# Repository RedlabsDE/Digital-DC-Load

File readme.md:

# Digtial DC Load Project

**key features:**
- linear constant curren sink
- galvanic isolated
- selectable operating range (high/low current/voltage)
- controlled via I2C
	- write & read load current
	- read load voltage
	- read additional external voltage
	- read temperature 
- manual option: set current via external voltage (or potentiometer)

**example application:**
- charge / discharge battery (control & measure current and voltage)
- measure & log current/voltage (use example setup to send data to PC)
- stess test of power supply

## Repository Overview
- **documentation**
  - application notes for constant current sink 
  - block diagram of PCB
  - screenshots and pictures of this project
- **firmware**
  - Arduino Example Project `DigitalLoadExample`, inlcuding a C++ class `RL021_DigitalLoad` for easy control
  - Example calibration procedure (manually step by step)
- **hardware**
  - **KiCAD** Project Folder including schematic, PCB layout and BOM
  - **schematic** and fabrication layer drawing as PDF
  - **datasheet** of used components
- **ui**
  - **GUI_CSS** is an example project for a simple pc-based user interface (written in processing)

## Hardware

**Order PCB:** https://aisler.net/p/YHESFYKF

### Jumper Settings
Via multiple jumpers the used operating ranges can be configured.

| Parameter | Jumper | open | closed |
| -- | -- | -- | -- |
| Current Control | JP1 | External analog signal | Digital via onboard DAC |
| I_load range | JP2 | low 0-1A | high 0-10A |
| V_load range | JP3 | high 0-24V | 0-4V |
| V_extern range | JP4 | high 0-24V | 0-4V |
| ADC I2C Addr (A2,A1,A0)| R8 | 0,0,1 | 0,0,0 |

# Example Setup

## Example Arduino Control

### Connect Arduino to CCS-PCB
| Signal      	| Arduino Pin    |
|---------------|-------|
| I2C_VDD (J2, pin1)    	| 5V 	|
| I2C_SDA (J2, pin2) 		| A4    |
| I2C_SCL (J2, pin3)    	| A5 	|
| I2C_GND (J2, pin4)    	| GND 	|
| SUPPLY_+5V (J1, pin1)    	| 5V 	|
| SUPPLY_GND (J1, pin2)    	| GND 	|

### Configure CCS-PCB according to your application
- See chapter "Jumper Settings" to select your operating range
- In the Arduino Code, the settings should be set according to physical state of the jumpers:
	```
		/// Write board jumper settings (like set on PCB)
		myLoad.SetJumperSetting(JP2_CURRENT,Jumper_Closed);
		myLoad.SetJumperSetting(JP3_VLOAD,Jumper_Open);
		myLoad.SetJumperSetting(JP4_VEXT,Jumper_Open);  
	```

## Example User Interface
An example PC-based user interface (written in "Processing"), for the use with the `firmware/DigitalLoadExample` project.

### Connect UI to Arduino ###
- The UI communicates via serial comport using simple ASCII character commands, so the communication could also be done manual.  
- The UI uses the first found COMPORT (to use another port, change this in the processing code)
	````
	  String portName = Serial.list()[0];
	  myPort = new Serial(this, portName, 115200);
	````
### Usage ###
In the "Control" page, all measured values are displayed in SI-units. The user can set the desired load current in mA.

In the "Calibration" page, the raw ADC values are displayed. The user can set the raw DAC value.

... find other projects: https://redlabs.de/

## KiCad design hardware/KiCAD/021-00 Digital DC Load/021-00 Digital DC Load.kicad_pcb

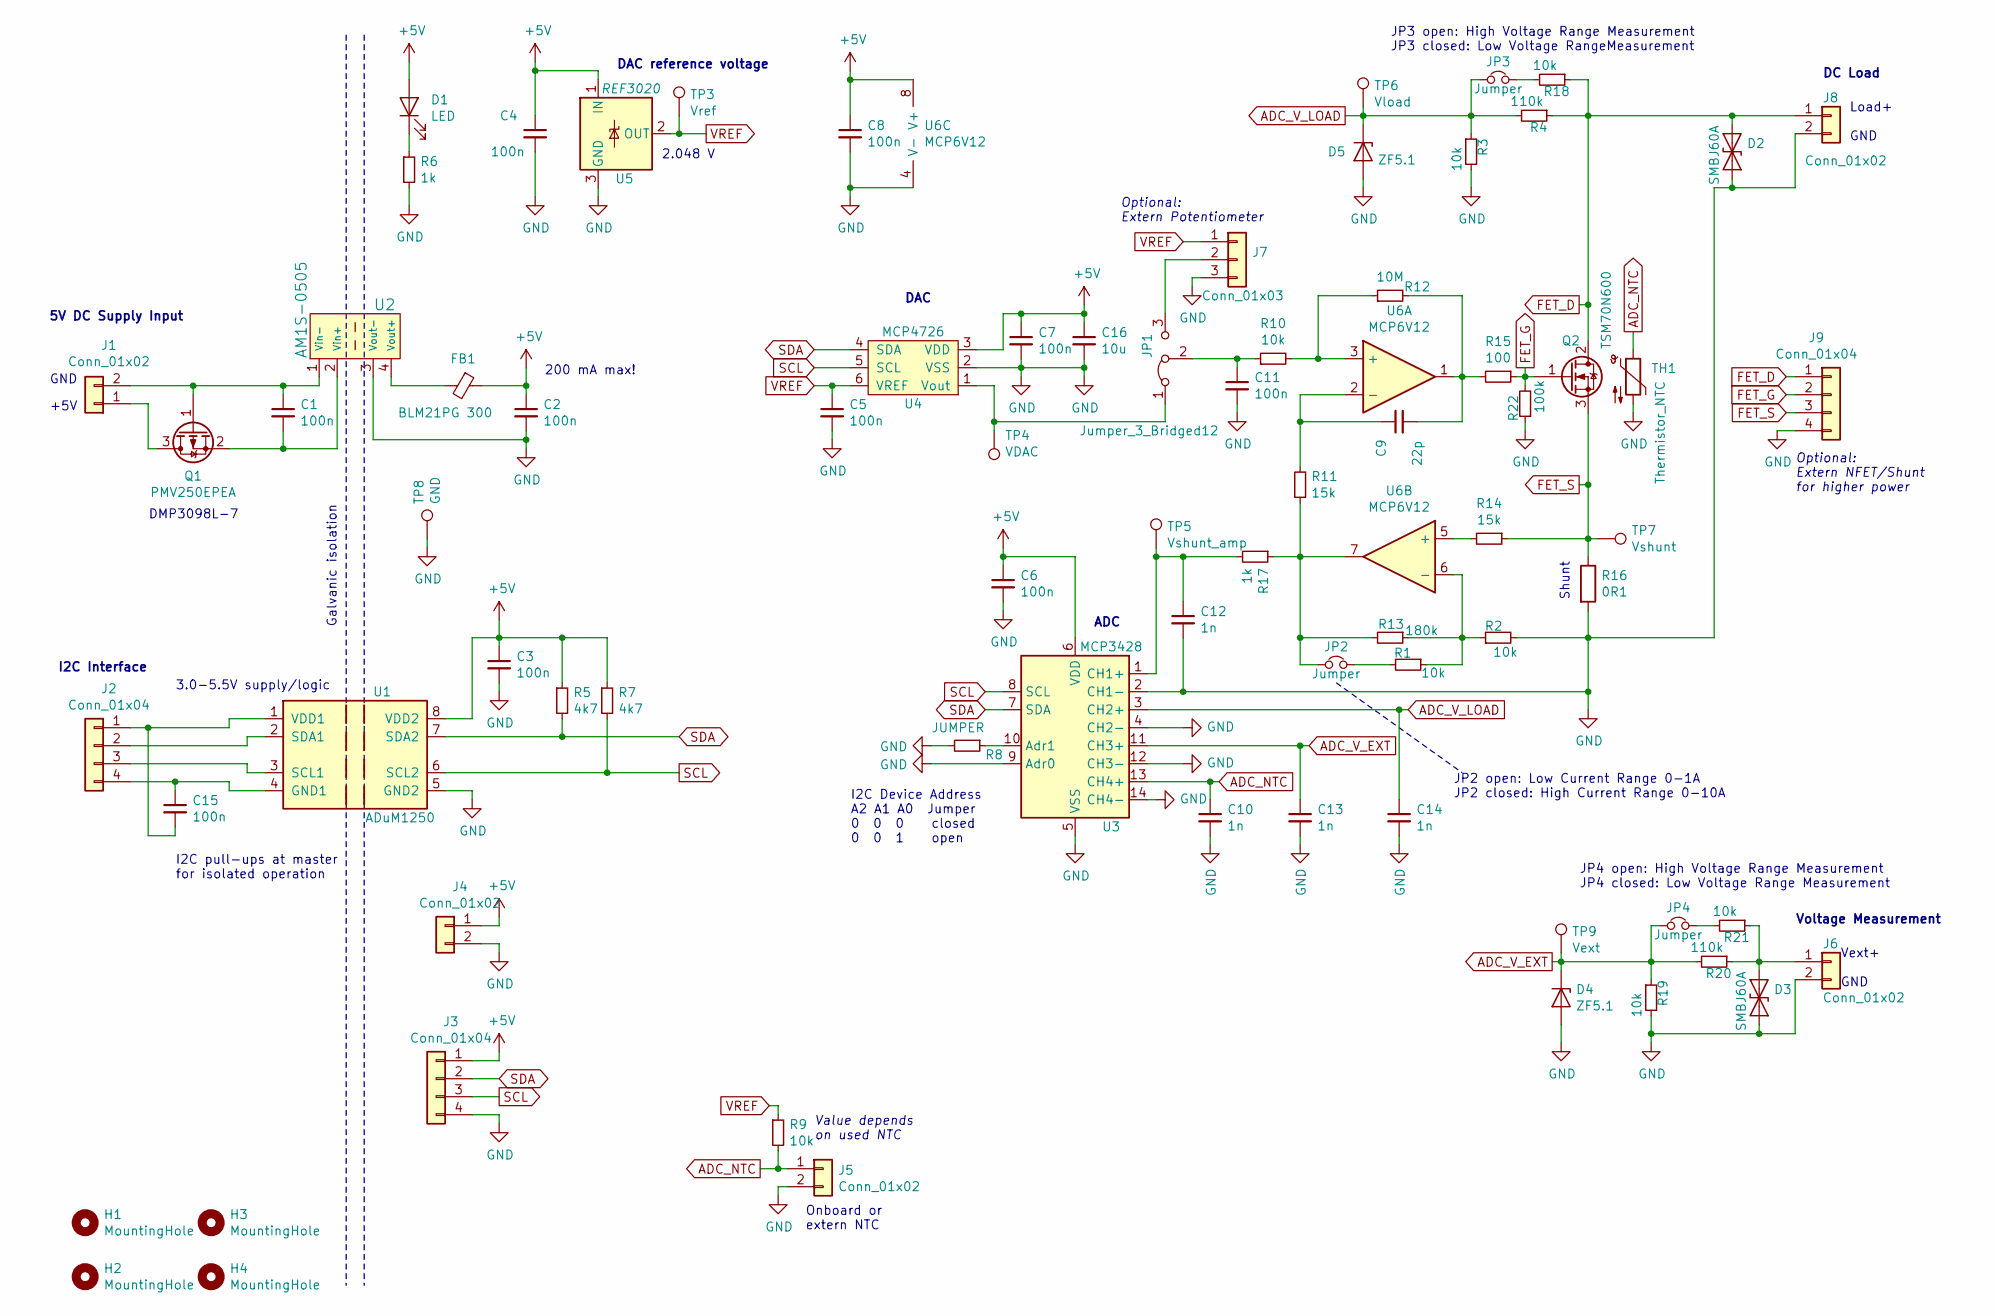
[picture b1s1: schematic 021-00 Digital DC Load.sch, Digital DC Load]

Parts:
C1, C2, C3, C4, C5, C6, C7, C8, C11, C15: 100n; C_0603
C9: 22p; C_0603
C10, C12, C13, C14: 1n; C_0603
C16: 10u; C_0805
D1: LED; LED_0805
D2, D3: SMBJ60A; D_SMB_bidirectional
D4, D5: ZF5.1; D_MiniMELF
FB1: BLM21PG 300; R_0805
H1, H2, H3, H4: MountingHole; MountingHole_2.7mm_M2.5_DIN965_Pad
J1, J4, J5, J6: Conn_01x02; JST_XH2P_oval_pads
J2, J3, J9: Conn_01x04; JST_XH4P_oval_pads
J7: Conn_01x03; JST_XH3P_oval_pads
J8: Conn_01x02; AKL_2_RM508_RND205-00199
JP1: Jumper_3_Bridged12; PIN_ARRAY_3X1_big_pads
JP2, JP3, JP4: Jumper; PIN_ARRAY_2X1_big_pads
Q1: PMV250EPEA; SOT-23
Q2: TSM70N600; TO-252-2
R1, R2, R3, R9, R10, R18, R19, R21: 10k; R_0603
R4, R20: 110k; R_0603
R5, R7: 4k7; R_0603
R6, R17: 1k; R_0603
R8: JUMPER; R_0603
R11, R14: 15k; R_0603
R12: 10M; R_0603
R13: 180k; R_0603
R15: 100; R_0603
R16: 0R1; R_1206_HandSoldering
R22: 100k; R_0603
TH1: Thermistor_NTC; R_0805
TP3: Vref; Measurement_Point_Round-SMD-Pad_Small
TP4: VDAC; Measurement_Point_Round-SMD-Pad_Small
TP5: Vshunt_amp; Measurement_Point_Round-SMD-Pad_Small
TP6: Vload; Measurement_Point_Round-SMD-Pad_Small
TP7: Vshunt; Measurement_Point_Round-SMD-Pad_Small
TP8: GND; Measurement_Point_Round-TH_Small
TP9: Vext; Measurement_Point_Round-SMD-Pad_Small
U1: ADuM1250; SOIC-8_3.9x4.9mm_Pitch1.27mm
U2: AM1S-0505; DCDC-Isolated-SIP4
U3: MCP3428; TSSOP-14_4.4x5mm_Pitch0.65mm
U4: MCP4726; SOT-23-6
U5: REF3020; SOT-23
U6: MCP6V12; MSOP-8_3x3mm_Pitch0.65mm

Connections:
+5V: C2.1, C3.1, C4.1, C6.1, C7.1, C8.1, C16.1, D1.2 (A), FB1.1, J3.1, J4.1, R5.1, R7.1, U1.8 (VDD2), U3.6 (VDD), U4.3 (VDD), U5.1 (IN), U6.8 (V+)
ADC_NTC: C10.1, J5.1, R9.2, TH1.1, U3.13 (CH4+)
ADC_V_EXT: C13.1, D4.1 (K), JP4.1, R19.1, R20.2, TP9.1, U3.11 (CH3+)
ADC_V_LOAD: C14.1, D5.1 (K), JP3.1, R3.1, R4.2, TP6.1, U3.3 (CH2+)
FET_D: D2.1 (A1), J8.1, J9.1, Q2.2 (D), R4.1, R18.1
FET_G: J9.2, Q2.1 (G), R15.1, R22.2
FET_S: J9.3, Q2.3 (S), R14.1, R16.1, TP7.1
GND: C2.2, C3.2, C4.2, C5.2, C6.2, C7.2, C8.2, C10.2, C11.2, C12.2, C13.2, C14.2, C16.2, D2.2 (A2), D3.2 (A2), D4.2 (A), D5.2 (A), J3.4, J4.2, J5.2, J6.2, J7.3, J8.2, J9.4, R2.2, R3.2, R6.2, R8.2, R16.2, R19.2, R22.1, TH1.2, TP8.1, U1.5 (GND2), U2.3 (Vout-), U3.2 (CH1-), U3.4 (CH2-), U3.5 (VSS), U3.9 (Adr0), U3.12 (CH3-), U3.14 (CH4-), U4.2 (VSS), U5.3 (GND), U6.4 (V-)
unnamed: C1.1, J1.2, Q1.1 (G), U2.1 (Vin-)
unnamed: C1.2, Q1.2 (S), U2.2 (Vin+)
unnamed: C9.1, R11.2, U6.2 (-)
unnamed: C9.2, R12.2, R15.2, U6.1
unnamed: C11.1, JP1.2 (C), R10.1
unnamed: C12.1, R17.2, TP5.1, U3.1 (CH1+)
unnamed: C15.1, J2.4, U1.4 (GND1)
unnamed: C15.2, J2.1, U1.1 (VDD1)
unnamed: D1.1 (K), R6.1
unnamed: D3.1 (A1), J6.1, R20.1, R21.1
unnamed: FB1.2, U2.4 (Vout+)
unnamed: J1.1, Q1.3 (D)
unnamed: J2.2, U1.2 (SDA1)
unnamed: J2.3, U1.3 (SCL1)
unnamed: J7.2, JP1.3 (B)
unnamed: JP1.1 (A), TP4.1, U4.1 (Vout)
unnamed: JP2.1, R11.1, R13.2, R17.1, U6.7
unnamed: JP2.2, R1.2
unnamed: JP3.2, R18.2
unnamed: JP4.2, R21.2
unnamed: R1.1, R2.1, R13.1, U6.6 (-)
unnamed: R8.1, U3.10 (Adr1)
unnamed: R10.2, R12.1, U6.3 (+)
unnamed: R14.2, U6.5 (+)
SCL: J3.3, R7.2, U1.6 (SCL2), U3.8 (SCL), U4.5 (SCL)
SDA: J3.2, R5.2, U1.7 (SDA2), U3.7 (SDA), U4.4 (SDA)
VREF: C5.1, J7.1, R9.1, TP3.1, U4.6 (VREF), U5.2 (OUT)

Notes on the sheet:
2.048 V
I2C Device Address A2 A1 A0 Jumper 0 0 0 closed 0 0 1 open
Shunt
Optional: Extern Potentiometer
Onboard or extern NTC
5V DC Supply Input
I2C Interface
3.0-5.5V supply/logic
I2C pull-ups at master for isolated operation
+5V
GND
200 mA max!
Optional: Extern NFET/Shunt for higher power
Galvanic isolation
DC Load
Value depends on used NTC
DAC
ADC
DAC reference voltage
Load+ GND
Voltage Measurement
Vext+ GND
JP4 open: High Voltage Range Measurement JP4 closed: Low Voltage Range Measurement
JP3 open: High Voltage Range Measurement JP3 closed: Low Voltage RangeMeasurement
JP2 open: Low Current Range 0-1A JP2 closed: High Current Range 0-10A
DMP3098L-7

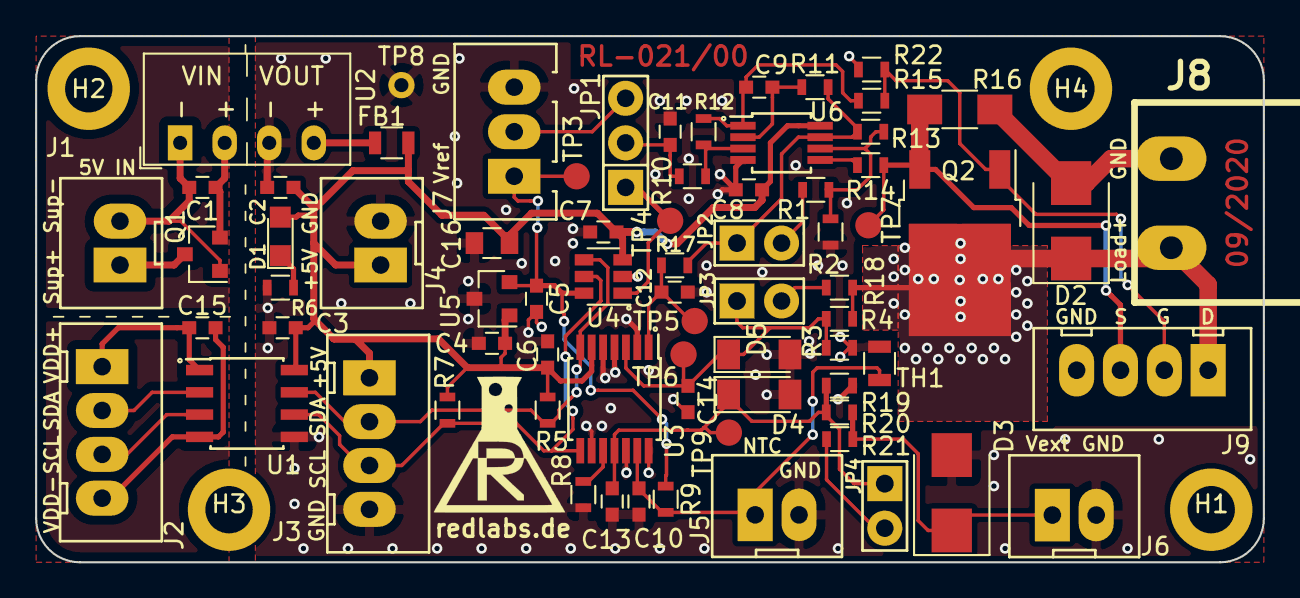
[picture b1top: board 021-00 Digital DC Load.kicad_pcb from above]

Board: 2 copper layers, 70.0 x 30.0 mm, 77 parts (0 on the bottom side), 35 nets.

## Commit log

2022-10-25 add aisler link to order PCB
2022-10-27 CCS-block-diagram.drawio aktualisiert
2025-12-11 add load power calculation to UI
2025-12-11 add brightness slider, apply gamma correction mith 700mA max
2025-12-11 send current value when brightness slider is changed
